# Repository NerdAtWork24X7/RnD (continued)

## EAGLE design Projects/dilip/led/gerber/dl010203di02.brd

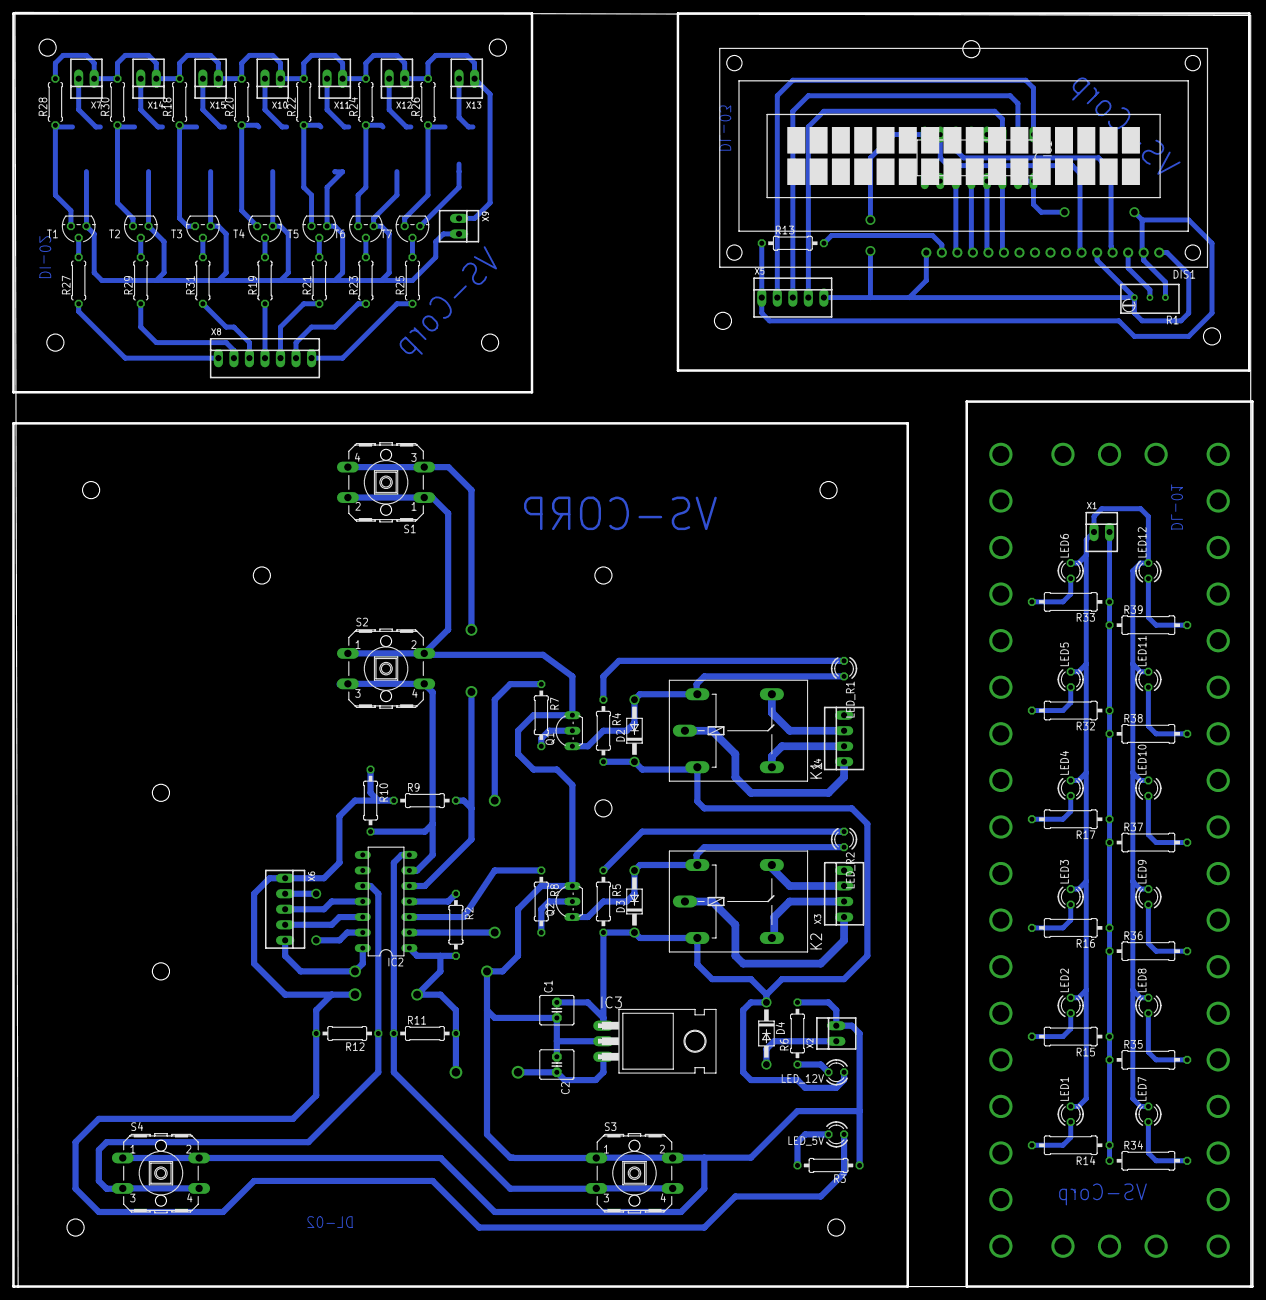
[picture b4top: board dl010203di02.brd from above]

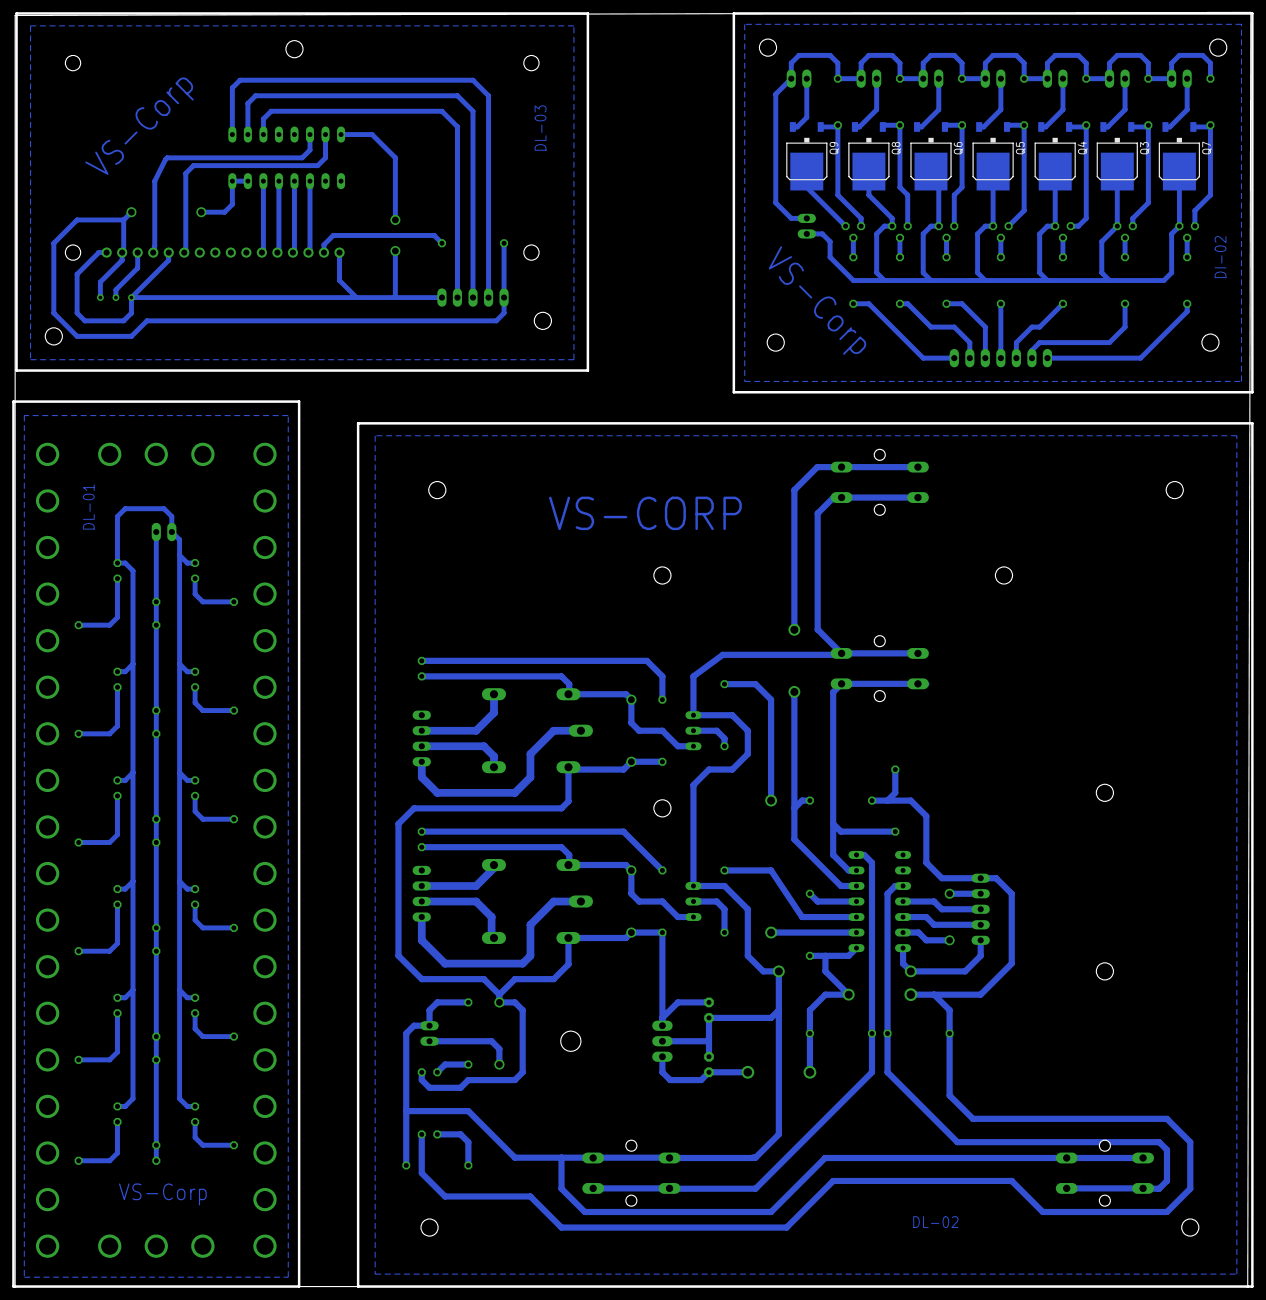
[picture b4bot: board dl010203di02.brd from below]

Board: 2 copper layers, 202.7 x 208.5 mm, 101 parts (7 on the bottom side), 85 nets.

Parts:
C1, C2: C2.5-6
D2, D3, D4: 1N4004; DO41-10
DIS1: TUXGR_16X2_R2
IC1: 4094N; DIL16
IC2: PIC16F676P; DIL14
IC3: 7805T; TO220H
K1, K2: G5L; G5LE
LED1, LED2, LED3, LED4, LED5, LED6, LED7, LED8, LED9, LED10, LED11, LED12: LED3MM
LED_5V, LED_12V: LED3MM
LED_R1, LED_R2: LED3MM
Q1, Q2: BC548; TO92-EBC
Q3, Q4, Q5, Q6, Q7, Q8, Q9: IRFR5305; D-PAK_TO252AA
R1: RTRIMT93YA
R2, R3, R4, R5, R6, R7, R8, R9, R10, R11, R12, R13: 0207/10
R14, R15, R16, R17, R32, R33, R34, R35, R36, R37, R38, R39: 0309/12
R18, R20, R22, R24, R26, R28, R30: 10k; 0207/7
R19, R21, R23, R25, R27, R29, R31: 1k; 0207/7
S1, S2, S3, S4: B3F-40XX
T1, T2, T3, T4, T5, T6, T7: 2N3904; TO92
X1, X2, X7, X9, X10, X11, X12, X13, X14, X15: 22-23-2021
X3, X4: 22-23-2041
X5, X6: 22-23-2051
X8: 7 pin connector; 22-23-2071

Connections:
E: DIS1.6, IC1.7
GND: C1.1, C2.1, IC2.14, IC3.2, Q1.E, Q2.E, R3.1, R6.2, S1.1, S1.2, S2.1, S2.2, S3.1, S3.2, S4.1, S4.2, X2.2, X6.5
GND1: Q3.4, Q4.4, Q5.4, Q6.4, Q7.4, Q8.4, Q9.4, T1.3, T2.3, T3.3, T4.3, T5.3, T6.3, T7.3, X9.2
unnamed: DIS1.3, R1.2
unnamed: DIS1.11, IC1.14
unnamed: DIS1.12, IC1.13
unnamed: DIS1.13, IC1.12
unnamed: DIS1.14, IC1.11
unnamed: IC2.11, X6.3
unnamed: IC2.13, X6.2
unnamed: IC2.12, X6.4
unnamed: IC2.4, R2.1
unnamed: Q1.B, R7.2
unnamed: D2.A, K1.2, LED_R1.K, Q1.C
unnamed: D3.A, K2.2, LED_R2.K, Q2.C
unnamed: Q2.B, R8.2
unnamed: K2.P, X3.1
unnamed: K2.S, X3.2
unnamed: K2.O, X3.3
unnamed: K1.S, X4.2
unnamed: K1.P, X4.1
unnamed: K1.O, X4.3
unnamed: D4.A, X2.1
unnamed: LED_5V.K, R3.2
unnamed: LED_R2.A, R5.1
unnamed: IC2.6, R10.2, S2.3, S2.4
unnamed: LED_R1.A, R4.1
unnamed: IC2.7, R11.1, S3.3, S3.4
unnamed: IC2.10, R12.1, S4.3, S4.4
unnamed: R14.1, R15.1, R16.1, R17.1, R32.1, R33.1, R34.1, R35.1, R36.1, R37.1, R38.1, R39.1, X1.2
unnamed: LED_12V.K, R6.1
unnamed: IC1.3, X5.4
unnamed: IC1.2, X5.3
unnamed: IC1.1, X5.2
unnamed: IC2.5, R9.2, S1.3, S1.4
unnamed: DIS1.15, R13.2
unnamed: LED1.K, LED2.K, LED3.K, LED4.K, LED5.K, LED6.K, LED7.K, LED8.K, LED9.K, LED10.K, LED11.K, LED12.K, X1.1
unnamed: C1.2, D2.C, D3.C, D4.C, IC3.1, K1.1, K2.1, LED_12V.A, R4.2, R5.2
unnamed: LED1.A, R14.2
unnamed: LED2.A, R15.2
unnamed: LED3.A, R16.2
unnamed: LED4.A, R17.2
unnamed: LED5.A, R32.2
unnamed: LED6.A, R33.2
unnamed: LED7.A, R34.2
unnamed: LED8.A, R35.2
unnamed: LED9.A, R36.2
unnamed: LED10.A, R37.2
unnamed: LED11.A, R38.2
unnamed: LED12.A, R39.2
unnamed: Q7.1, R28.1, T1.1
unnamed: R27.2, T1.2
unnamed: Q7.3, X7.2
unnamed: R27.1, X8.1
unnamed: Q3.1, R30.1, T2.1
unnamed: R29.2, T2.2
unnamed: Q3.3, X14.2
unnamed: Q4.1, R18.1, T3.1
unnamed: R31.2, T3.2
unnamed: Q4.3, X15.2
unnamed: R31.1, X8.3
unnamed: Q5.1, R20.1, T4.1
unnamed: R19.2, T4.2
unnamed: Q5.3, X10.2
unnamed: R19.1, X8.4
unnamed: Q6.1, R22.1, T5.1
unnamed: R21.2, T5.2
unnamed: Q6.3, X11.2
unnamed: R21.1, X8.5
unnamed: Q8.1, R24.1, T6.1
unnamed: R23.2, T6.2
unnamed: Q8.3, X12.2
unnamed: R23.1, X8.6
unnamed: Q9.1, R26.1, T7.1
unnamed: R25.2, T7.2
unnamed: Q9.3, X13.2
unnamed: R25.1, X8.7
unnamed: R29.1, X8.2
RELAY1: IC2.2, R7.1
RELAY2: IC2.3, R8.1
RS: DIS1.4, IC1.6
VCC: C2.2, IC2.1, IC3.3, LED_5V.A, R2.2, R9.1, R10.1, R11.2, R12.2, X6.1
VDD: DIS1.2, IC1.15, IC1.16, R1.1, R13.1, X5.1
VDD1: R18.2, R20.2, R22.2, R24.2, R26.2, R28.2, R30.2, X7.1, X9.1, X10.1, X11.1, X12.1, X13.1, X14.1, X15.1
VSS: DIS1.1, DIS1.5, DIS1.16, IC1.8, R1.3, X5.5
